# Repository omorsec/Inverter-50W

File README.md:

# Inverter-50W
Inverter Design using an Arduino Nano

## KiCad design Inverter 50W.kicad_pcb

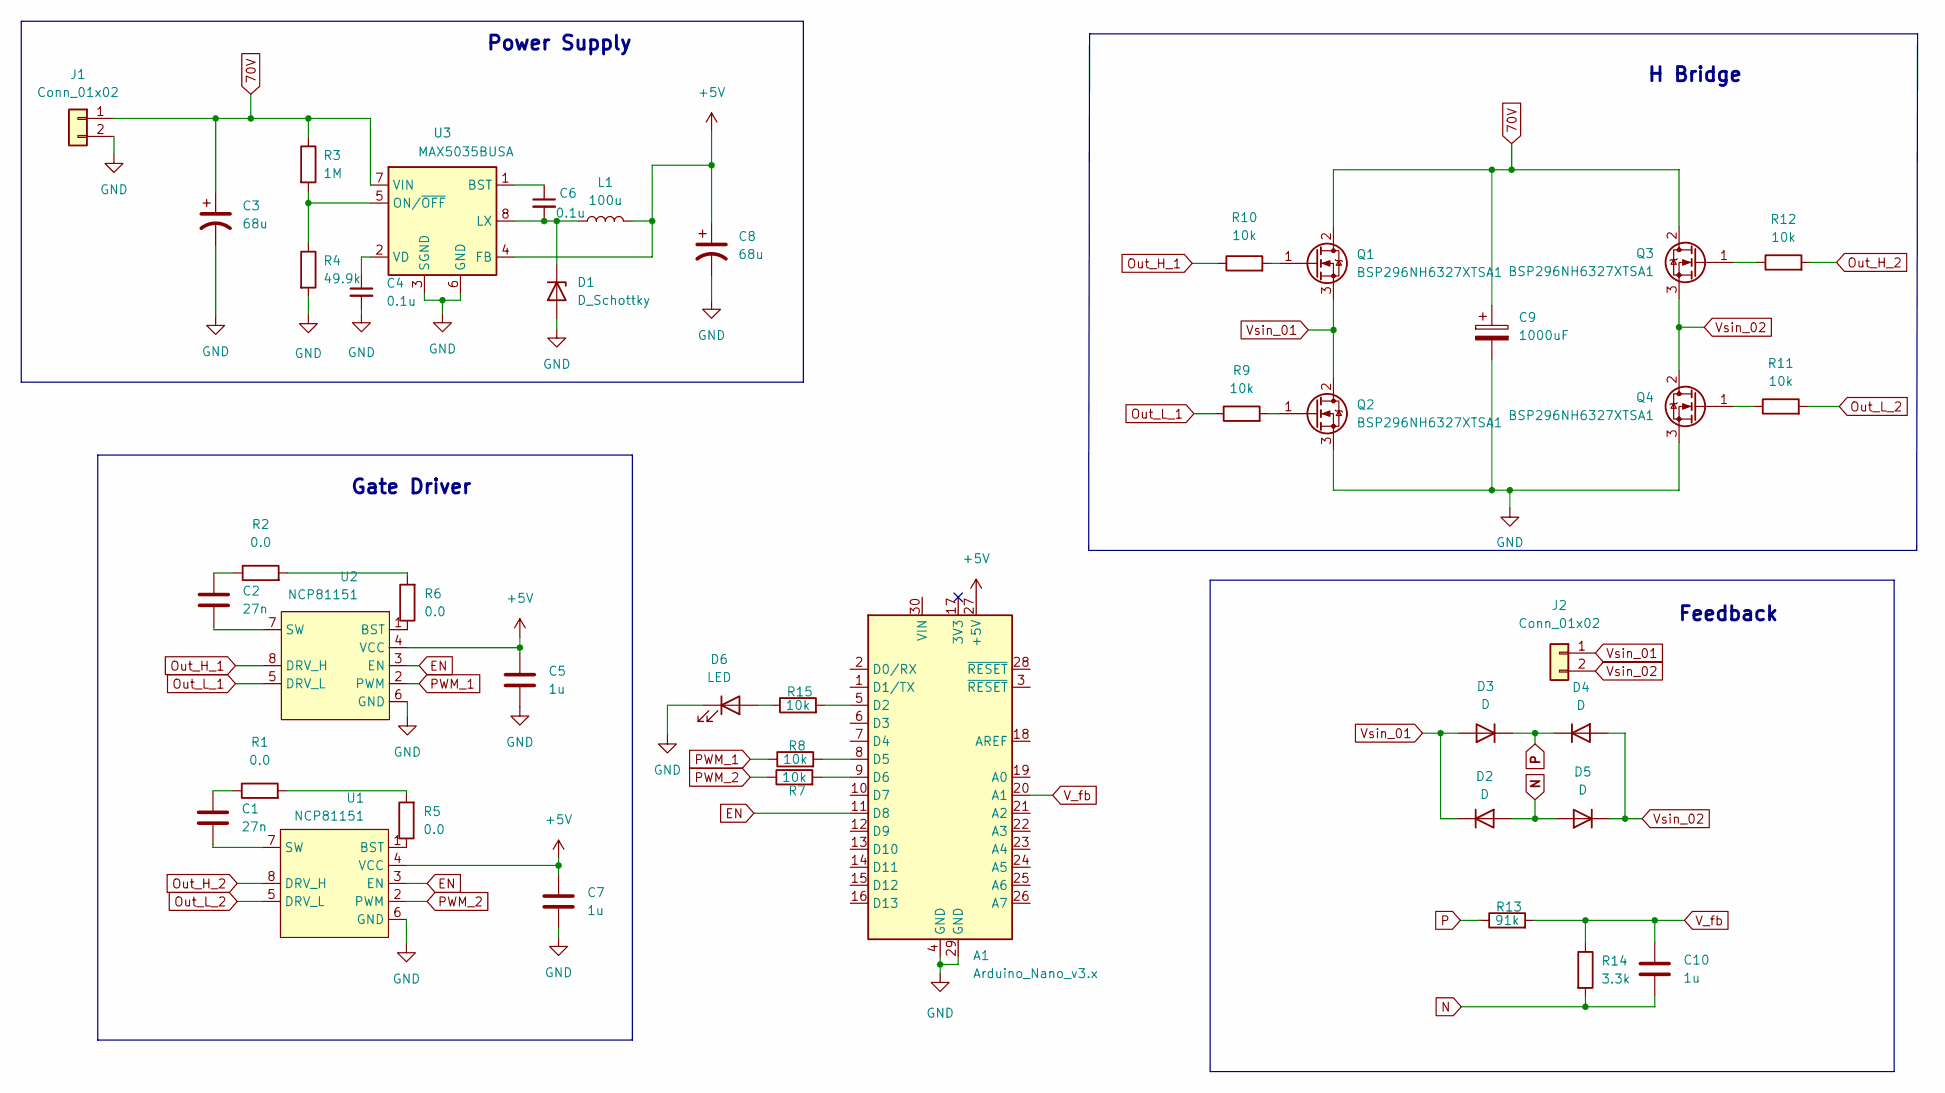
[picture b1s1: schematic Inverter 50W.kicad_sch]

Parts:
A1: Arduino_Nano_v3.x; Arduino_Nano; Manufacturer part no A000005
C1, C2: 27n; C_0603_1608Metric; Manufacturer part no 06035C273KAT2A
C3: 68u; CP_Radial_D12.5mm_P5.00mm; Manufacturer part no EEUFC2A680
C4, C6: 0.1u; C_0805_2012Metric; Manufacturer part no CC0805KRX7R7BB104
C5, C7, C10: 1u; C_0805_2012Metric; Manufacturer part no C0805X105K4RACTU
C8: 68u; CP_Elec_6.3x5.2; Manufacturer part no 865080443009
C9: 1000uF; CP_Radial_D18.0mm_P7.50mm; Manufacturer part no ECA2AM102
D1: D_Schottky; DO-221(AC); Manufacturer part no VSSAF510HM3
D2, D3, D4, D5: D; D_SMA; Manufacturer part no S2BA-13-F
D6: LED; LED_1206_3216Metric; Manufacturer part no 3216SGC
J1, J2: Conn_01x02; TerminalBlock_Phoenix_MKDS-1,5-2_1x02_P5.00mm_Horizontal; Manufacturer part no CTB55VG/2
L1: 100u; L_6.0x6.0_4.5; Manufacturer part no VLS6045AF-101M
Q1, Q2, Q3, Q4: BSP296NH6327XTSA1; SOT-223-3_TabPin2; Manufacturer part no BSP296NH6327XTSA1
R1, R2, R5, R6: 0.0; R_0603_1608Metric; Manufacturer part no RC0603JR-070RL
R3: 1M; R_0805_2012Metric; Manufacturer part no CRCW08051M00FKEA
R4: 49.9k; R_0805_2012Metric; Manufacturer part no PCF0805R-49K9BT1
R7, R8, R9, R10, R11, R12, R15: 10k; R_0805_2012Metric; Manufacturer part no ASC0805-10KFT5
R13: 91k; R_0805_2012Metric; Manufacturer part no CRCW080591K0FKEA
R14: 3.3k; R_0603_1608Metric; Manufacturer part no RC0603FR-073K3L
U1, U2: NCP81151; Manufacturer part no NCP81151
U3: MAX5035BUSA; SOIC-8_3.9x4.9mm_P1.27mm; Manufacturer part no MAX5035BUSA

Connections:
70V: C3.1, C9.1, J1.1, Q1.2 (D), Q3.2 (D), R3.1, U3.7 (VIN)
+5V: A1.27 (+5V), C5.1, C7.1, C8.1, L1.2, U1.4 (VCC), U2.4 (VCC), U3.4 (FB)
<NO NET>: A1.4 (GND), A1.29 (GND), C3.2, C4.2, C5.2, C7.2, C8.2, C9.2, D1.2 (A), D6.1 (K), J1.2, Q2.3 (S), Q4.3 (S), R4.2, U1.6 (GND), U1.9, U2.6 (GND), U2.9, U3.3 (SGND), U3.6 (GND)
EN: A1.11 (D8), U1.3 (EN), U2.3 (EN)
N: C10.2, D2.2 (A), D5.2 (A), R14.2
unnamed: A1.5 (D2), R15.2
unnamed: A1.8 (D5), R8.2
unnamed: A1.9 (D6), R7.2
unnamed: C1.1, R1.1
unnamed: C1.2, U1.7 (SW)
unnamed: C2.1, R2.1
unnamed: C2.2, U2.7 (SW)
unnamed: C4.1, U3.2 (VD)
unnamed: C6.1, U3.1 (BST)
unnamed: C6.2, D1.1 (K), L1.1, U3.8 (LX)
unnamed: D6.2 (A), R15.1
unnamed: Q1.1 (G), R10.2
unnamed: Q2.1 (G), R9.2
unnamed: Q3.1 (G), R12.1
unnamed: Q4.1 (G), R11.1
unnamed: R1.2, R5.2
unnamed: R2.2, R6.2
unnamed: R3.2, R4.1, U3.5 (ON/~OFF)
unnamed: R5.1, U1.1 (BST)
unnamed: R6.1, U2.1 (BST)
Out_H_1: R10.1, U2.8 (DRV_H)
Out_H_2: R12.2, U1.8 (DRV_H)
Out_L_1: R9.1, U2.5 (DRV_L)
Out_L_2: R11.2, U1.5 (DRV_L)
P: D3.1 (K), D4.1 (K), R13.1
PWM_1: R8.1, U2.2 (PWM)
PWM_2: R7.1, U1.2 (PWM)
V_fb: A1.20 (A1), C10.1, R13.2, R14.1
Vsin_01: D2.1 (K), D3.2 (A), J2.1, Q1.3 (S), Q2.2 (D)
Vsin_02: D4.2 (A), D5.1 (K), J2.2, Q3.3 (S), Q4.2 (D)

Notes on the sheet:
Power Supply
Feedback
H Bridge
Gate Driver

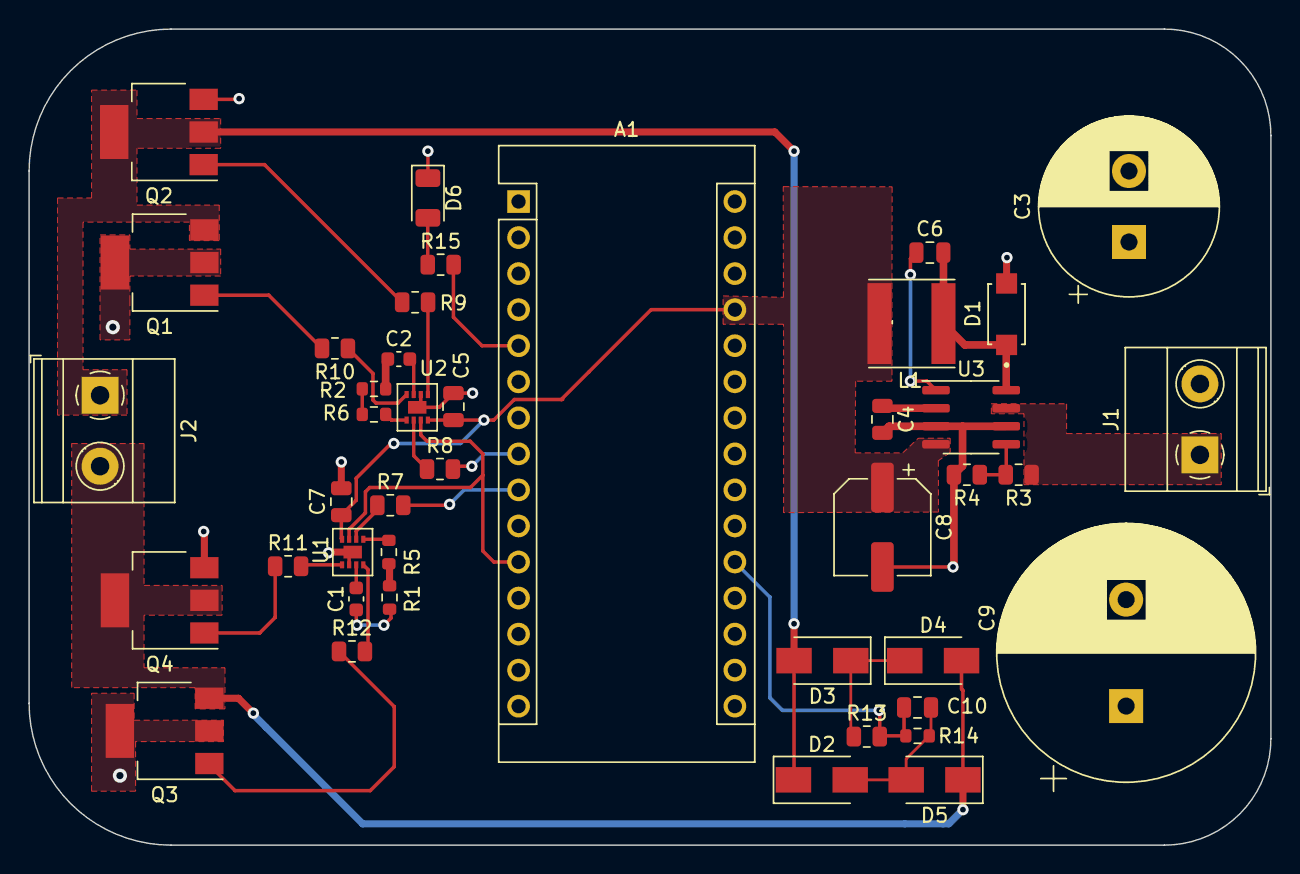
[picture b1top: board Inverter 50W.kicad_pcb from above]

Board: 4 copper layers, 87.5 x 57.5 mm, 42 parts (0 on the bottom side), 35 nets.

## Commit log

2023-01-13 Final Update Inverter Design
